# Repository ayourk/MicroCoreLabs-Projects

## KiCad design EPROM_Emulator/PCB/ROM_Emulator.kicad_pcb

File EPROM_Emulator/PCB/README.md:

# EPROM_Emulator/PCB
EPROM Emulator - Small PCB which uses [Teensy 4.0](https://www.pjrc.com/store/teensy40.html) to emulate up a 64KB 27C512 EPROM

This is PCB was designed in KiCAD 6.10 and uses MicroCore Lab's EPROM Emulator as a base.  All traces were redone and 2 solder jumper pads were added to the front along the right side of the board to make the board Chip Select(CS) pin configurable.

The Nabu uses Pin 20 for Chip Select (lower solder jumper) and the IBM PC uses the Pin 22 for Chip Select (upper solder jumper) which is what the board was originally designed for.

Please solder closed the appropriate solder jumper pads before use. Neither solder jumpers are connected by default!

Per the Build of Materials, in addition to the PCBs, you will want:

1. 1x [Teensy 4.0](https://www.pjrc.com/store/teensy40.html) which is the workhorse of this project.
2. 2x [IC Header](http://store.go4retro.com/ic-header/) which is top/bottom jumper pins in IC socket form.
3. 3x Bus Transceivers via either [Digikey](https://www.digikey.com/en/products/detail/texas-instruments/SN74LVT245BDBR/373941) or [Mouser](https://www.mouser.com/ProductDetail/Texas-Instruments/SN74LVT245BDBR?qs=FM6NhYOeeBVRIGHSKl2GVg%3D%3D). I couldn't find the equivalent in stock via [LCSC](https://www.lcsc.com/search?q=SN74LVT245BDBR) so that they could be surface mounted via JLCPCB. :frowning_face:

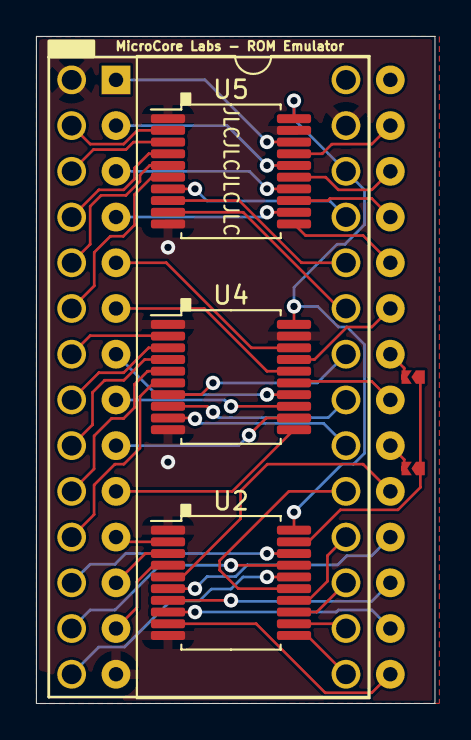
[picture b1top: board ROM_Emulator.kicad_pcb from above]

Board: 2 copper layers, 22.1 x 37.1 mm, 7 parts (0 on the bottom side), 53 nets.

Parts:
REF_D9, REF_D9#2: SolderJumper-2_P1.3mm_Open_TrianglePad1.0x0.75mm
U1: 27C512; DIP-28_W15.24mm
U2, U4, U5: 74LS245; SSOP-20_5.3x7.2mm_P0.65mm
U3: Teensy4.0; Teensy40

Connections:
+3V3: U2.20 (VCC), U3.31 (3V3), U4.20 (VCC), U5.20 (VCC)
CS_20: REF_D9.2, U1.20 (~CE)
CS_22: REF_D9#2.2, U1.22 (~OE)
GND: U1.14 (GND), U2.1 (A->B), U2.10 (GND), U3.1 (GND), U3.32 (GND), U4.1 (A->B), U4.10 (GND), U4.19 (CE), U5.1 (A->B), U5.10 (GND), U5.19 (CE)
OE_n: REF_D9.1, REF_D9#2.1, U2.19 (CE)
V3_A0: U3.25 (18_A4_SDA0), U4.9 (A7)
V3_A1: U3.26 (19_A5_SCL0), U4.8 (A6)
V3_A2: U3.27 (20_A6_TX5_LRCLK1), U4.7 (A5)
V3_A3: U3.11 (9_OUT1C), U4.6 (A4)
V3_A4: U3.9 (7_RX2_OUT1A), U4.4 (A2)
V3_A5: U3.7 (5_IN2), U4.2 (A0)
V3_A6: U3.29 (22_A8_CTX1), U5.8 (A6)
V3_A7: U3.6 (4_BCLK2), U5.6 (A4)
V3_A8: U3.30 (23_A9_CRX1_MCLK1), U5.7 (A5)
V3_A9: U3.28 (21_A7_RX5_BCLK1), U5.9 (A7)
V3_A10: U3.10 (8_TX2_IN1), U4.5 (A3)
V3_A11: U3.8 (6_OUT1D), U4.3 (A1)
V3_A12: U3.4 (2_OUT2), U5.4 (A2)
V3_A13: U3.5 (3_LRCLK2), U5.5 (A3)
V3_A14: U3.3 (1_TX1_CTX2_MISO1), U5.3 (A1)
V3_A15: U3.2 (0_RX1_CRX2_CS1), U5.2 (A0)
V3_D0: U2.18 (B0), U3.12 (10_CS_MQSR)
V3_D1: U2.17 (B1), U3.13 (11_MOSI_CTX1)
V3_D2: U2.16 (B2), U3.14 (12_MISO_MQSL)
V3_D3: U2.11 (B7), U3.20 (13_SCK_CRX1_LED)
V3_D4: U2.12 (B6), U3.21 (14_A0_TX3_SPDIF_OUT)
V3_D5: U2.13 (B5), U3.22 (15_A1_RX3_SPDIF_IN)
V3_D6: U2.14 (B4), U3.23 (16_A2_RX4_SCL1)
V3_D7: U2.15 (B3), U3.24 (17_A3_TX4_SDA1)
V5_A0: U1.10 (A0), U4.11 (B7)
V5_A1: U1.9 (A1), U4.12 (B6)
V5_A2: U1.8 (A2), U4.13 (B5)
V5_A3: U1.7 (A3), U4.14 (B4)
V5_A4: U1.6 (A4), U4.16 (B2)
V5_A5: U1.5 (A5), U4.18 (B0)
V5_A6: U1.4 (A6), U5.12 (B6)
V5_A7: U1.3 (A7), U5.14 (B4)
V5_A8: U1.25 (A8), U5.13 (B5)
V5_A9: U1.24 (A9), U5.11 (B7)
V5_A10: U1.21 (A10), U4.15 (B3)
V5_A11: U1.23 (A11), U4.17 (B1)
V5_A12: U1.2 (A12), U5.16 (B2)
V5_A13: U1.26 (A13), U5.15 (B3)
V5_A14: U1.27 (A14), U5.17 (B1)
V5_A15: U1.1 (A15), U5.18 (B0)
V5_D0: U1.11 (D0), U2.2 (A0)
V5_D1: U1.12 (D1), U2.3 (A1)
V5_D2: U1.13 (D2), U2.4 (A2)
V5_D3: U1.15 (D3), U2.9 (A7)
V5_D4: U1.16 (D4), U2.8 (A6)
V5_D5: U1.17 (D5), U2.7 (A5)
V5_D6: U1.18 (D6), U2.6 (A4)
V5_D7: U1.19 (D7), U2.5 (A3)

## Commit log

2023-02-06 Move BOM to PCB root.
2023-02-06 Clarification about solder jumper locations.
2023-02-06 Add links to components.
2023-02-06 Updating BOM quantity.
2023-02-12 PDF of Schematic; Don't expect this to be up to date!
